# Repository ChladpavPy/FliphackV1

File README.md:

# Fliphack V1

A custom, pocket sized hardware multitool inspired by the Flipper Zero. Built to learn custom PCB design and integrate specific modules like GPS and long-range RF, including also the other Filpper Zero modules. Designed entirely from scratch in KiCad and Fusion 360.

## Project Features

* **Microcontroller:** ESP32-S3 WROOM 1U (16MB Flash, 8MB PSRAM) with external wifi antena
* **Display:** 1.69" IPS TFT LCD (ST7789 SPI)
* **Wireless and RF:** Sub-GHz (CC1101), 2.4GHz (nRF24L01+PA+LNA), NFC/RFID (PN532), and also external WIFI antena
* **Navigation:** GPS (NEO-8M)
* **Storage:** MicroSD Card module for SD card
* **Infrared:** High-power IR Transmitter (Vishay TSAL6400) and 38kHz IR Receiver
* **Controls:** 5-way navigation switch + SMT tactile buttons for BOOT and RST
* **Power:** External battery - 3.7V 800mAh, Size: 802540 (8x25x40mm) and USB C interface
* **Case:** Custom 3D modeled thick enclosure with snap-fit parts and M3 inserts

## Gallery

### Build Preview

### Assembly Preview

### 3D PCB Render

### PCB Routing

### Schematic

---

## Bill of Materials (BOM)

| Component | Qty | Description | LCSC Part # / Note |
| :--- | :---: | :--- | :--- |
| **ESP32-S3-WROOM-1U** | 5 | MCU (16MB Flash, 8MB PSRAM, U.FL connector) | N16R8 Version - This is a problem, I wanted to ship it assembled with the pcb from jlcpcb, but unfortunately it must be ordered with standard pcb, that means that the price would rise from approximately 33 USD to crazy over 100 USD - So my plan is to order it from LCSC.com and ship it with the LCSC parts in the same box, because they support it, I think -  https://www.lcsc.com/product-detail/C3013946.html?s_z=n_esp32-s3-wroom-1u / or there is the LCSC part number - C3013946|
| **2.4GHz Antenna** + Pigtail | 1 |3dBi WiFi Antenna with 17cm U.FL IPX to SMA cable	Essential for ESP32-S3-1U -| https://a.aliexpress.com/_EItoDMg | 
| **1.69" SPI Display** | 1 | LCD with ST7789 driver (240x280px) | SPI Interface https://a.aliexpress.com/_EIgOvRA| 
| **CC1101 Module** | 1 | Sub-GHz RF module (with SMA antenna) | E07-M1101D https://a.aliexpress.com/_Ey9DMVW |
| **nRF24L01+PA+LNA Module** | 1 | 2.4GHz RF module (Mouse Hijacking) | https://a.aliexpress.com/_Ew8TYLa  |
| **PN532 Module** | 1 | NFC/RFID 13.56MHz module | https://a.aliexpress.com/_ExXcsbE |
| **Neo-8M GPS Module** | 1 | GPS module with ceramic patch antenna | https://a.aliexpress.com/_EvsK2kc |
| **MicroSD Card Module** | 1 | For offline data logging | https://a.aliexpress.com/_EHdpg1A |
| **TSOP4838** | 10 | 38kHz Infrared Receiver | https://a.aliexpress.com/_EzLWQ5W |
| **Vishay TSAL6400** | 10 | 5mm 940nm THT Infrared LEDs (High power)|https://a.aliexpress.com/_EIPCbXW| | **Passive Piezzo Buzzer** | 1 | 12x9.5mm, RM7.6 OR smaller diameter, just make sure that the pins diameter is ok, otherwise you would have to add more solder
| **Passive Piezzo Buzzer** | 10 | diameter size 12 * 9.5 or smaller |https://a.aliexpress.com/_ExtD1xe|
| **TS-1187A Buttons** | 10 | SMT Tactile Switches (3x6mm footprint) | **C318884** (Basic Part - included in JLCPCB assembly) |
| **LiPo Battery** | 1 | 3.7V 800mAh, Size: 802540 (8x25x40mm) |https://a.aliexpress.com/_EQnfApW |

### Mechanical & Assembly
| Item | Qty | Specification | Purpose |
| :--- | :---: | :--- | :--- |
| **M3 Heat-set Inserts** | 4 | Brass inserts (M3x3x4.2mm) | Case mounting |
| **M3 Screws** | 4 | M3x6mm (Button Head) | Enclosure assembly |
| **3D Printed Case** | 1 | Custom PLA/PETG Enclosure | Files in `3D_Models` |

---

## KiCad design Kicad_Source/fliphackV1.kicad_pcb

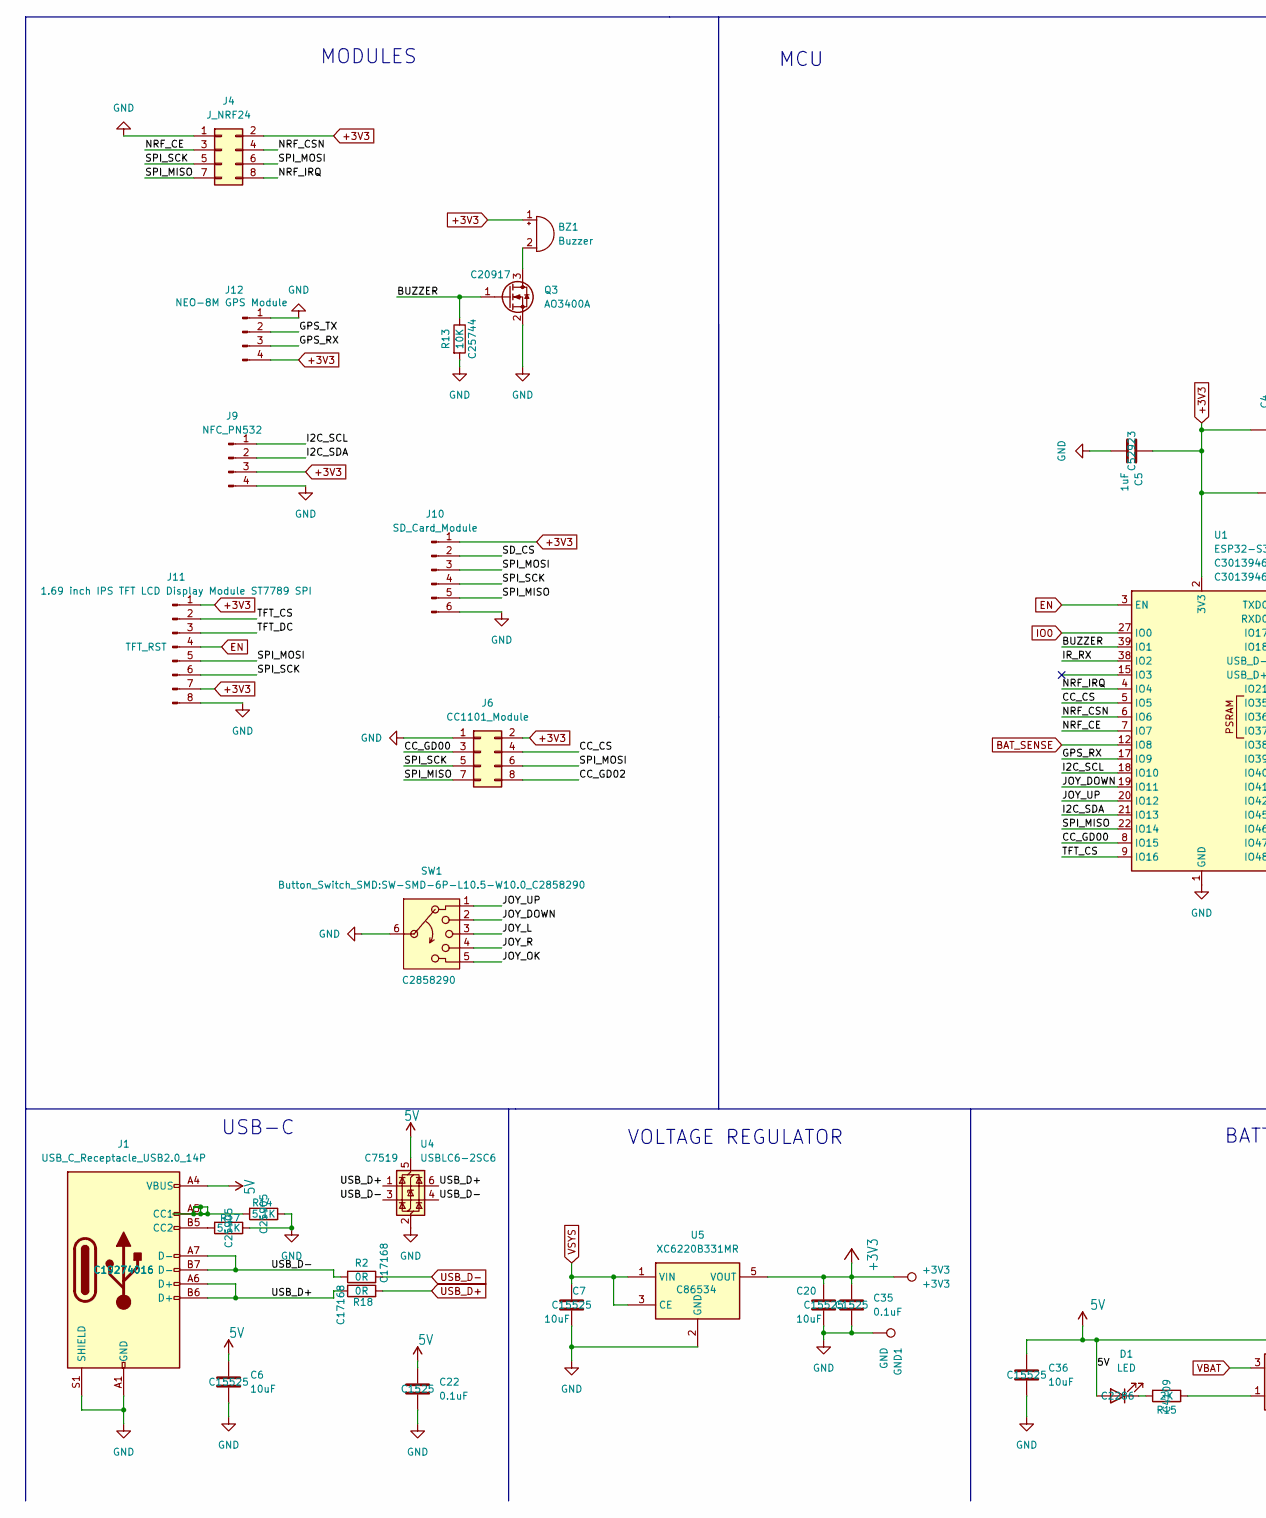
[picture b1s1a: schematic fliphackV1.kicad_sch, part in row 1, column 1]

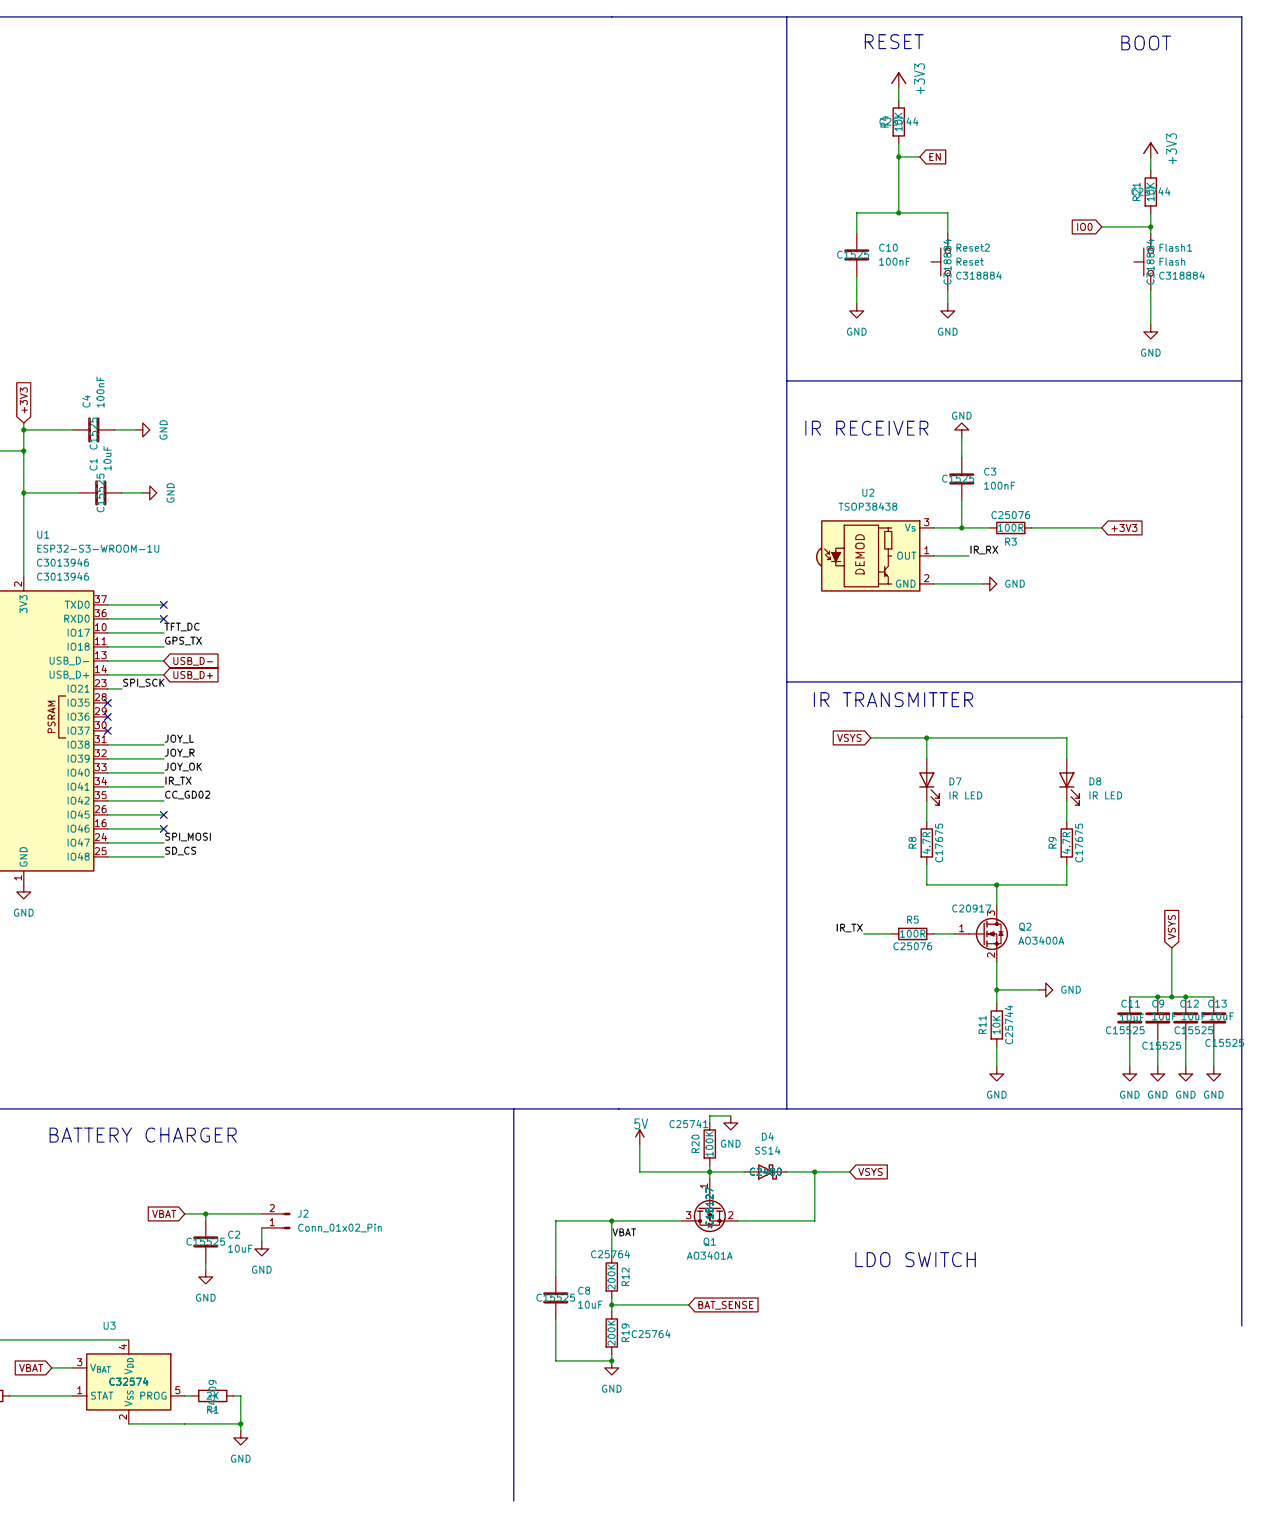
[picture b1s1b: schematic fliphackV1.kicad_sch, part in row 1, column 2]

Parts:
+3V3: +3V3; TestPoint_Pad_D1.0mm
BZ1: Buzzer; Buzzer_12x9.5RM7.6
C1, C2, C6, C7, C8, C9, C11, C12, C13, C20, C36: 10uF; C_0402_1005Metric; MNF PART NUMBER C15525; LCSC C15525
C3, C4, C10: 100nF; C_0402_1005Metric; MNF PART NUMBER C1525; LCSC C1525
C5: 1uF; C_0402_1005Metric; MNF PART NUMBER C52923; LCSC C52923
C22, C35: 0.1uF; C_0402_1005Metric; MNF PART NUMBER C1525; LCSC C1525
D1: LED; LED_0603_1608Metric; MNF PART NUMBER C2286; LCSC C2286
D4: SS14; D_SMA; MNF PART NUMBER C2480; LCSC C2480
D7, D8: IR LED; LED_D5.0mm
Flash1: Flash; SW_Push_1P1T_XKB_TS-1187A; MNF PART NUMBER C318884; LCSC C318884
GND1: GND; TestPoint_Pad_D1.0mm
J1: USB_C_Receptacle_USB2.0_14P; USB_C_Receptacle_HCTL_HC-TYPE-C-16P-01A; MNF PART NUMBER C19274016; LCSC C19274016
J2: Conn_01x02_Pin; PinSocket_1x02_P2.54mm_Vertical
J4: J_NRF24; PinHeader_2x04_P2.54mm_Vertical
J6: CC1101_Module; PinHeader_2x04_P2.54mm_Vertical
J9: NFC_PN532; PinHeader_1x04_P2.54mm_Vertical
J10: SD_Card_Module; PinHeader_1x06_P2.54mm_Vertical
J11: 1.69 inch IPS TFT LCD Display Module ST7789 SPI; PinHeader_1x08_P2.54mm_Vertical
J12: NEO-8M GPS Module; PinHeader_1x04_P2.54mm_Vertical
Q1: AO3401A; SOT-23; MNF PART NUMBER C15127; LCSC C15127
Q2, Q3: AO3400A; SOT-23; MNF PART NUMBER C20917; LCSC C20917
R1, R15: 2K; R_0402_1005Metric; MNF PART NUMBER C4109; LCSC C4109
R2, R18: 0R; R_0402_1005Metric; MNF PART NUMBER C17168; LCSC C17168
R3, R5: 100R; R_0402_1005Metric; MNF PART NUMBER C25076; LCSC C25076
R4, R11, R13, R21: 10K; R_0402_1005Metric; MNF PART NUMBER C25744; LCSC C25744
R8, R9: 4.7R; R_0805_2012Metric; MNF PART NUMBER C17675; LCSC C17675
R12, R19: 200K; R_0402_1005Metric; MNF PART NUMBER C25764; LCSC C25764
R14, R17: 5.1K; R_0402_1005Metric; MNF PART NUMBER C25905; LCSC C25905
R20: 100K; R_0402_1005Metric; MNF PART NUMBER C25741; LCSC C25741
Reset2: Reset; SW_Push_1P1T_XKB_TS-1187A; MNF PART NUMBER C318884; LCSC C318884
SW1: Button_Switch_SMD:SW-SMD-6P-L10.5-W10.0_C2858290; SW-SMD-6P-L10.5-W10.0_C2858290; MNF PART NUMBER C2858290; LCSC C2858290
U1: ESP32-S3-WROOM-1U; MNF PART NUMBER C3013946; LCSC C3013946
U2: TSOP38438; Vishay_MINICAST-3Pin
U3: MCP73831-2-OT; SOT-23-5; MNF PART NUMBER C32574; LCSC C32574
U4: USBLC6-2SC6; SOT-23-6; MNF PART NUMBER C7519; LCSC C7519
U5: XC6220B331MR; SOT-23-5; MNF PART NUMBER C86534; LCSC C86534

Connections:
5V: C6.1, C22.1, C36.1, D1.2 (A), D4.2 (A), J1.A4 (VBUS), J1.A9 (VBUS), J1.B4 (VBUS), J1.B9 (VBUS), Q1.1 (G), R20.2, U3.4 (V_{DD}), U4.5 (VBUS)
+3V3: +3V3.1, BZ1.1 (+), C1.1, C4.1, C5.1, C20.1, C35.1, J4.2, J6.2, J9.3, J10.1, J11.1, J11.7, J12.4, R3.2, R4.1, R21.1, U1.2 (3V3), U5.5 (VOUT)
/BUZZER: Q3.1 (G), R13.1, U1.39 (IO1)
/CC_CS: J6.4, U1.5 (IO5)
/CC_GD00: J6.3, U1.8 (IO15)
/CC_GD02: J6.8, U1.35 (IO42)
/GPS_RX: J12.3, U1.17 (IO9)
/GPS_TX: J12.2, U1.11 (IO18)
/I2C_SCL: J9.1, U1.18 (IO10)
/I2C_SDA: J9.2, U1.21 (IO13)
/IR_RX: U1.38 (IO2), U2.1 (OUT)
/IR_TX: R5.2, U1.34 (IO41)
/JOY_DOWN: SW1.2, U1.19 (IO11)
/JOY_L: SW1.3, U1.31 (IO38)
/JOY_OK: SW1.5, U1.33 (IO40)
/JOY_R: SW1.4, U1.32 (IO39)
/JOY_UP: SW1.1, U1.20 (IO12)
/NRF_CE: J4.3, U1.7 (IO7)
/NRF_CSN: J4.4, U1.6 (IO6)
/NRF_IRQ: J4.8, U1.4 (IO4)
/SD_CS: J10.2, U1.25 (IO48)
/SPI_MISO: J4.7, J6.7, J10.5, U1.22 (IO14)
/SPI_MOSI: J4.6, J6.6, J10.3, J11.5, U1.24 (IO47)
/SPI_SCK: J4.5, J6.5, J10.4, J11.6, U1.23 (IO21)
/TFT_CS: J11.2, U1.9 (IO16)
/TFT_DC: J11.3, U1.10 (IO17)
BAT_SENSE: R12.2, R19.1, U1.12 (IO8)
EN: C10.1, J11.4, R4.2, Reset2.2, U1.3 (EN)
GND: C1.2, C2.2, C3.1, C4.2, C5.2, C6.2, C7.2, C8.2, C9.2, C10.2, C11.2, C12.2, C13.2, C20.2, C22.2, C35.2, C36.2, Flash1.1, GND1.1, J1.A1 (GND), J1.A12 (GND), J1.B1 (GND), J1.B12 (GND), J1.S1 (SHIELD), J2.1, J4.1, J6.1, J9.4, J10.6, J11.8, J12.1, Q2.2 (S), Q3.2 (S), R1.1, R11.1, R11.2, R13.2, R14.1, R17.1, R19.2, R20.1, Reset2.1, SW1.6 (Common), U1.1 (GND), U1.40 (GND), U1.41 (GND), U2.2 (GND), U3.2 (V_{SS}), U4.2 (GND), U5.2 (GND)
IO0: Flash1.2, R21.2, U1.27 (IO0)
unnamed: BZ1.2 (-), Q3.3 (D)
unnamed: D1.1 (K), R15.2
unnamed: D7.1 (K), R8.1
unnamed: D8.1 (K), R9.1
unnamed: J1.A5 (CC1), R14.2
unnamed: J1.B5 (CC2), R17.2
unnamed: Q2.3 (D), R8.2, R9.2
unnamed: Q2.1 (G), R5.1
unnamed: C3.2, R3.1, U2.3 (Vs)
unnamed: R1.2, U3.5 (PROG)
unnamed: R15.1, U3.1 (STAT)
USB_D+: J1.A6 (D+), J1.B6 (D+), R18.1, R18.2, U1.14 (USB_D+), U4.1 (I/O1), U4.6 (I/O1)
USB_D-: J1.A7 (D-), J1.B7 (D-), R2.1, R2.2, U1.13 (USB_D-), U4.3 (I/O2), U4.4 (I/O2)
VBAT: C2.1, C8.1, J2.2, Q1.3 (D), R12.1, U3.3 (V_{BAT})
VSYS: C7.1, C9.1, C11.1, C12.1, C13.1, D4.1 (K), D7.2 (A), D8.2 (A), Q1.2 (S), U5.1 (VIN), U5.3 (CE)

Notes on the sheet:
BATTERY CHARGER
VOLTAGE REGULATOR
BOOT
RESET
MODULES
LDO SWITCH
MCU
IR TRANSMITTER
IR RECEIVER
USB-C

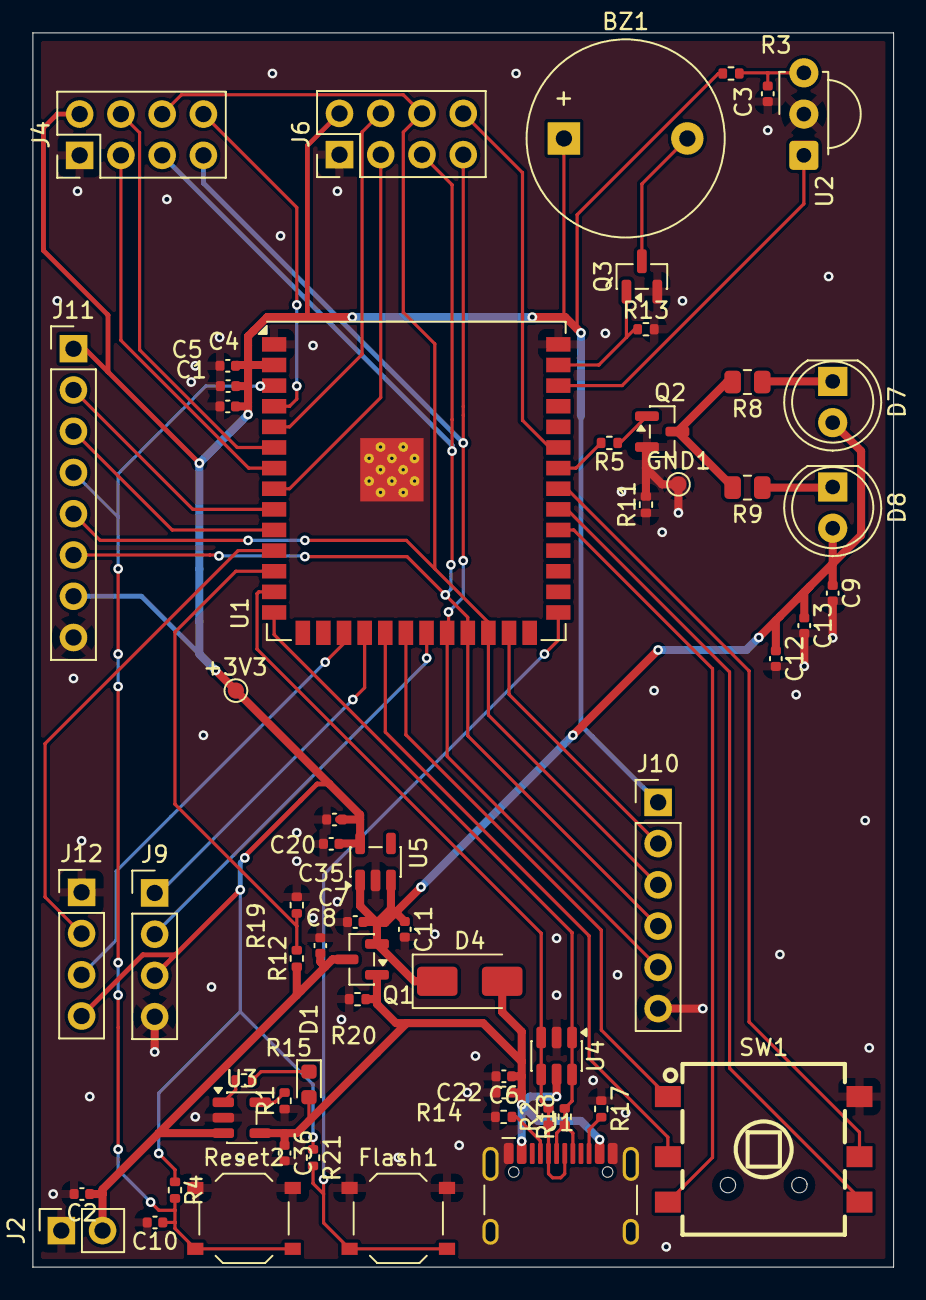
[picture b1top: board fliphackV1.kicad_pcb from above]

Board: 2 copper layers, 53.0 x 76.0 mm, 60 parts (0 on the bottom side), 45 nets.

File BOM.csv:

"Reference","Qty","Value","DNP","Exclude from BOM","Exclude from Board","Footprint","Datasheet"
"+3V3","1","+3V3","","","","TestPoint:TestPoint_Pad_D1.0mm","~"
"BZ1","1","Buzzer","","","","Buzzer_Beeper:Buzzer_12x9.5RM7.6","~"
"C1,C2,C6,C7,C8,C9,C11,C12,C13,C20,C36","11","10uF","","","","Capacitor_SMD:C_0402_1005Metric","~"
"C3,C4,C10","3","100nF","","","","Capacitor_SMD:C_0402_1005Metric","~"
"C5","1","1uF","","","","Capacitor_SMD:C_0402_1005Metric","~"
"C22,C35","2","0.1uF","","","","Capacitor_SMD:C_0402_1005Metric","~"
"D1","1","LED","","","","LED_SMD:LED_0603_1608Metric","~"
"D4","1","SS14","","","","Diode_SMD:D_SMA","https://www.vishay.com/docs/88746/ss12.pdf"
"D7,D8","2","IR LED","","","","LED_THT:LED_D5.0mm","~"
"Flash1","1","Flash","","","","Button_Switch_SMD:SW_Push_1P1T_XKB_TS-1187A","~"
"GND1","1","GND","","","","TestPoint:TestPoint_Pad_D1.0mm","~"
"J1","1","USB_C_Receptacle_USB2.0_14P","","","","Connector_USB:USB_C_Receptacle_HCTL_HC-TYPE-C-16P-01A","https://www.usb.org/sites/default/files/documents/usb_type-c.zip"
"J2","1","Conn_01x02_Pin","","","","Connector_PinSocket_2.54mm:PinSocket_1x02_P2.54mm_Vertical","~"
"J4","1","J_NRF24","","","","Connector_PinHeader_2.54mm:PinHeader_2x04_P2.54mm_Vertical","~"
"J6","1","CC1101_Module","","","","Connector_PinHeader_2.54mm:PinHeader_2x04_P2.54mm_Vertical","~"
"J9","1","NFC_PN532","","","","Connector_PinHeader_2.54mm:PinHeader_1x04_P2.54mm_Vertical","~"
"J10","1","SD_Card_Module","","","","Connector_PinHeader_2.54mm:PinHeader_1x06_P2.54mm_Vertical","~"
"J11","1","1.69 inch IPS TFT LCD Display Module ST7789 SPI","","","","Connector_PinHeader_2.54mm:PinHeader_1x08_P2.54mm_Vertical","~"
"J12","1","NEO-8M GPS Module","","","","Connector_PinHeader_2.54mm:PinHeader_1x04_P2.54mm_Vertical","~"
"Q1","1","AO3401A","","","","Package_TO_SOT_SMD:SOT-23","http://www.aosmd.com/pdfs/datasheet/AO3401A.pdf"
"Q2,Q3","2","AO3400A","","","","Package_TO_SOT_SMD:SOT-23","~"
"R1,R15","2","2K","","","","Resistor_SMD:R_0402_1005Metric","~"
"R2,R18","2","0R","","","","Resistor_SMD:R_0402_1005Metric","~"
"R3,R5","2","100R","","","","Resistor_SMD:R_0402_1005Metric","~"
"R4,R11,R13,R21","4","10K","","","","Resistor_SMD:R_0402_1005Metric","~"
"R8,R9","2","4.7R","","","","Resistor_SMD:R_0805_2012Metric","~"
"R12,R19","2","200K","","","","Resistor_SMD:R_0402_1005Metric","~"
"R14,R17","2","5.1K","","","","Resistor_SMD:R_0402_1005Metric","~"
"R20","1","100K","","","","Resistor_SMD:R_0402_1005Metric","~"
"Reset2","1","Reset","","","","Button_Switch_SMD:SW_Push_1P1T_XKB_TS-1187A","~"
"SW1","1","Button_Switch_SMD:SW-SMD-6P-L10.5-W10.0_C2858290","","","","Button_Switch_SMD:SW-SMD-6P-L10.5-W10.0_C2858290",""
"U1","1","ESP32-S3-WROOM-1U","","","","RF_Module:ESP32-S3-WROOM-1U","https://www.espressif.com/sites/default/files/documentation/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"
"U2","1","TSOP4838","","","","OptoDevice:Vishay_MINICAST-3Pin","http://www.vishay.com/docs/82491/tsop382.pdf"
"U3","1","MCP73831-2-OT","","","","Package_TO_SOT_SMD:SOT-23-5","http://ww1.microchip.com/downloads/en/DeviceDoc/20001984g.pdf"
"U4","1","USBLC6-2SC6","","","","Package_TO_SOT_SMD:SOT-23-6","https://www.st.com/resource/en/datasheet/usblc6-2.pdf"
"U5","1","XC6220B331MR","","","","Package_TO_SOT_SMD:SOT-23-5","https://www.torexsemi.com/file/xc6220/XC6220.pdf"

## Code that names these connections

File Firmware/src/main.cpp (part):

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#include <Wire.h>
#include <Adafruit_PN532.h>

#define JOY_UP    12  
#define JOY_LEFT  11 
#define JOY_DOWN  38  
#define JOY_RIGHT 40  
#define JOY_OK    39  

#define GPS_RX_PIN 18 
#define GPS_TX_PIN 9
#define BUZZER_PIN 1 

#define SPI_SCK_PIN  21
#define SPI_MISO_PIN 14
#define SPI_MOSI_PIN 47

#define SD_CS_PIN    48
#define TFT_CS_PIN   16

#define CC_CS_PIN    5 
#define CC_GDO0_PIN  15
#define CC_GDO2_PIN  42

#define NRF_CSN_PIN  6 
#define NRF_CE_PIN   7  
#define NRF_IRQ_PIN  4  

#define IR_RX_PIN    2

#define PN_532_SCL_PIN 10
#define PN_532_SDA_PIN 13
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
TFT_eSPI tft = TFT_eSPI(); 

CC1101 cc1101 = new Module(CC_CS_PIN, CC_GDO0_PIN, RADIOLIB_NC, CC_GDO2_PIN);
nRF24 nrf24 = new Module(NRF_CSN_PIN, NRF_IRQ_PIN, NRF_CE_PIN);

TinyGPSPlus gps;
bool nmea_paused = false;
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lv_group_t * g; 
lv_obj_t * current_screen = NULL;

IRrecv irrecv(IR_RX_PIN);
decode_results results;

uint64_t learn_signal_value = 0;
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}

void playTone(int freq, int duration) {
   tone(BUZZER_PIN, freq, duration);
   delay(duration + 30); 
}

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}

static bool cc1101BeginRadio() {
    digitalWrite(TFT_CS_PIN, HIGH);
    digitalWrite(SD_CS_PIN, HIGH);
    digitalWrite(NRF_CSN_PIN, HIGH);

    cc1101_receiving = false;
    cc1101_last_state = cc1101.begin(current_cc_freq, 4.8, 48.0, 26.0, 10, 32);
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    Serial.begin(115200);
    Serial.println("\n--- START HARDWARU ---");

    pinMode(TFT_CS_PIN, OUTPUT);  digitalWrite(TFT_CS_PIN, HIGH);
    pinMode(SD_CS_PIN, OUTPUT);   digitalWrite(SD_CS_PIN, HIGH);
    pinMode(CC_CS_PIN, OUTPUT);   digitalWrite(CC_CS_PIN, HIGH);
    pinMode(NRF_CSN_PIN, OUTPUT); digitalWrite(NRF_CSN_PIN, HIGH);

    SPI.begin(SPI_SCK_PIN, SPI_MISO_PIN, SPI_MOSI_PIN, SD_CS_PIN);
    delay(100); 

    Serial.print("CC1101 SubGHz... ");
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    delay(50);

    Serial.print("SD Karta... ");
    sd_card_ok = SD.begin(SD_CS_PIN, SPI, 4000000);
    if (!sd_card_ok) Serial.println("CHYBA!"); else Serial.printf("OK (%llu MB)\n", SD.cardSize() / (1024 * 1024));
    Serial.print("PN532 NFC (I2C)... ");

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    irrecv.enableIRIn();  
    Serial.println("IR Prijimac... OK");

    Serial1.begin(9600, SERIAL_8N1, GPS_RX_PIN, GPS_TX_PIN);
    
    WiFi.mode(WIFI_STA);
    WiFi.disconnect();
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        disp_drv.hor_res = screenWidth; disp_drv.ver_res = screenHeight; disp_drv.flush_cb = my_disp_flush; disp_drv.draw_buf = &draw_buf;
        lv_disp_drv_register(&disp_drv);

        pinMode(JOY_UP, INPUT_PULLUP); pinMode(JOY_DOWN, INPUT_PULLUP); pinMode(JOY_LEFT, INPUT_PULLUP);
        pinMode(JOY_RIGHT, INPUT_PULLUP); pinMode(JOY_OK, INPUT_PULLUP);

        gpio_reset_pin(GPIO_NUM_39); gpio_set_direction(GPIO_NUM_39, GPIO_MODE_INPUT); gpio_set_pull_mode(GPIO_NUM_39, GPIO_PULLUP_ONLY);
        gpio_reset_pin(GPIO_NUM_40); gpio_set_direction(GPIO_NUM_40, GPIO_MODE_INPUT); gpio_set_pull_mode(GPIO_NUM_40, GPIO_PULLUP_ONLY);
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        current_screen = lv_scr_act(); load_group_for_screen(current_screen);
        isBooted = true;
        if (BUZZER_ON){
            pinMode(BUZZER_PIN, OUTPUT);
            playTone(1000, 150); 
        }
        Serial.println("====== FLIPHACK O.S. PRIPRAVEN ======");
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                    if (found && uid_len > 0) {

                        if (BUZZER_ON){
                            pinMode(BUZZER_PIN, OUTPUT);
                            playTone(1000, 150); 
                        }
                    
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
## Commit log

2026-03-02 Add Bill of Materials to README
    Added a Bill of Materials section detailing components and quantities for the project.
2026-03-02 Revise README with updated BOM and assembly details
    Updated the Bill of Materials with new components and specifications. Added a new section for Mechanical & Assembly.
2026-03-03 Add LiPo Battery specifications to README
2026-03-03 Update component part numbers in README
2026-03-03 Update nRF24L01+ module name to nRF24L01+PA+LNA
2026-03-06 Enhance BOM with assembly notes for components
    Updated the Bill of Materials to include assembly notes for components.
2026-03-07 Add assembly preview image to README
2026-03-07 Update image path and format in README
2026-03-07 Add more assembly preview images
    Added additional assembly preview images to the README.
2026-03-07 Add assembly preview image to README
    Added an additional assembly preview image to the README.
2026-03-07 Update README with new images and PCB render
    Added additional assembly preview images and a 3D PCB render to the README.
2026-03-07 Update PCB 3D image in README
2026-03-07 Rename Snímek obrazovky 2026-03-02 201856.png to pcb3d1.png
2026-03-07 Rename Snímek obrazovky 2026-03-04 182400.png to pcb3d2.png
2026-03-07 Rename Snímek obrazovky 2026-03-07 082603.png to pcb3d3.png
2026-03-07 Rename Snímek obrazovky 2026-03-07 082728.png to pcb3d4.png
2026-03-07 Rename Snímek obrazovky 2026-03-07 082822.png to pcb3d5.png
2026-03-07 Rename Snímek obrazovky 2026-03-07 082907.png to pcb3d6.png
2026-03-07 Rename Snímek obrazovky 2026-03-07 083031.png to pcb3d7.png
2026-03-07 Create Firmware
2026-03-07 Add TFT display initialization code
    Initialize TFT display with setup and loop functions.
2026-03-07 Revise project title and add project description
    Updated project name formatting and added a brief description.
2026-03-07 Update README with project features and details
    Expanded project description and added features list.
2026-03-07 Fix formatting of infrared component description
2026-03-07 Update Passive Piezo Buzzer description and link
2026-03-07 Update BOM with detailed ESP32-S3-WROOM-1U info
    Expanded description for ESP32-S3-WROOM-1U component regarding sourcing and pricing.
2026-03-07 Update PCB images in README
    Removed an outdated PCB 3D image and updated PCB 2D image reference.
2026-03-07 Fix image path for PCB 2D in README
2026-03-07 Update quantity of ESP32-S3-WROOM-1U to 5
2026-03-07 Update TSOP4838 quantity from 1 to 10
2026-03-07 Update quantities and specifications in README
2026-03-07 Update README with 2.4GHz Antenna details
    Added details for 2.4GHz Antenna with pigtail to components list.
2026-03-15 Remove GND1 entry from BOM.csv
    Removed GND1 entry from BOM.
2026-03-19 Enhance BOM entry for ESP32-S3-WROOM-1U
    Updated the description for ESP32-S3-WROOM-1U with additional LCSC part number.
2026-03-19 Fix LCSC part number formatting in BOM section
2026-06-22 Update Firmware
2026-06-28 Create LICENSE
2026-06-28 Rename image.png to build1.png
2026-06-28 Rename image.png to build2.png
2026-06-28 Rename image.png to build3.png
